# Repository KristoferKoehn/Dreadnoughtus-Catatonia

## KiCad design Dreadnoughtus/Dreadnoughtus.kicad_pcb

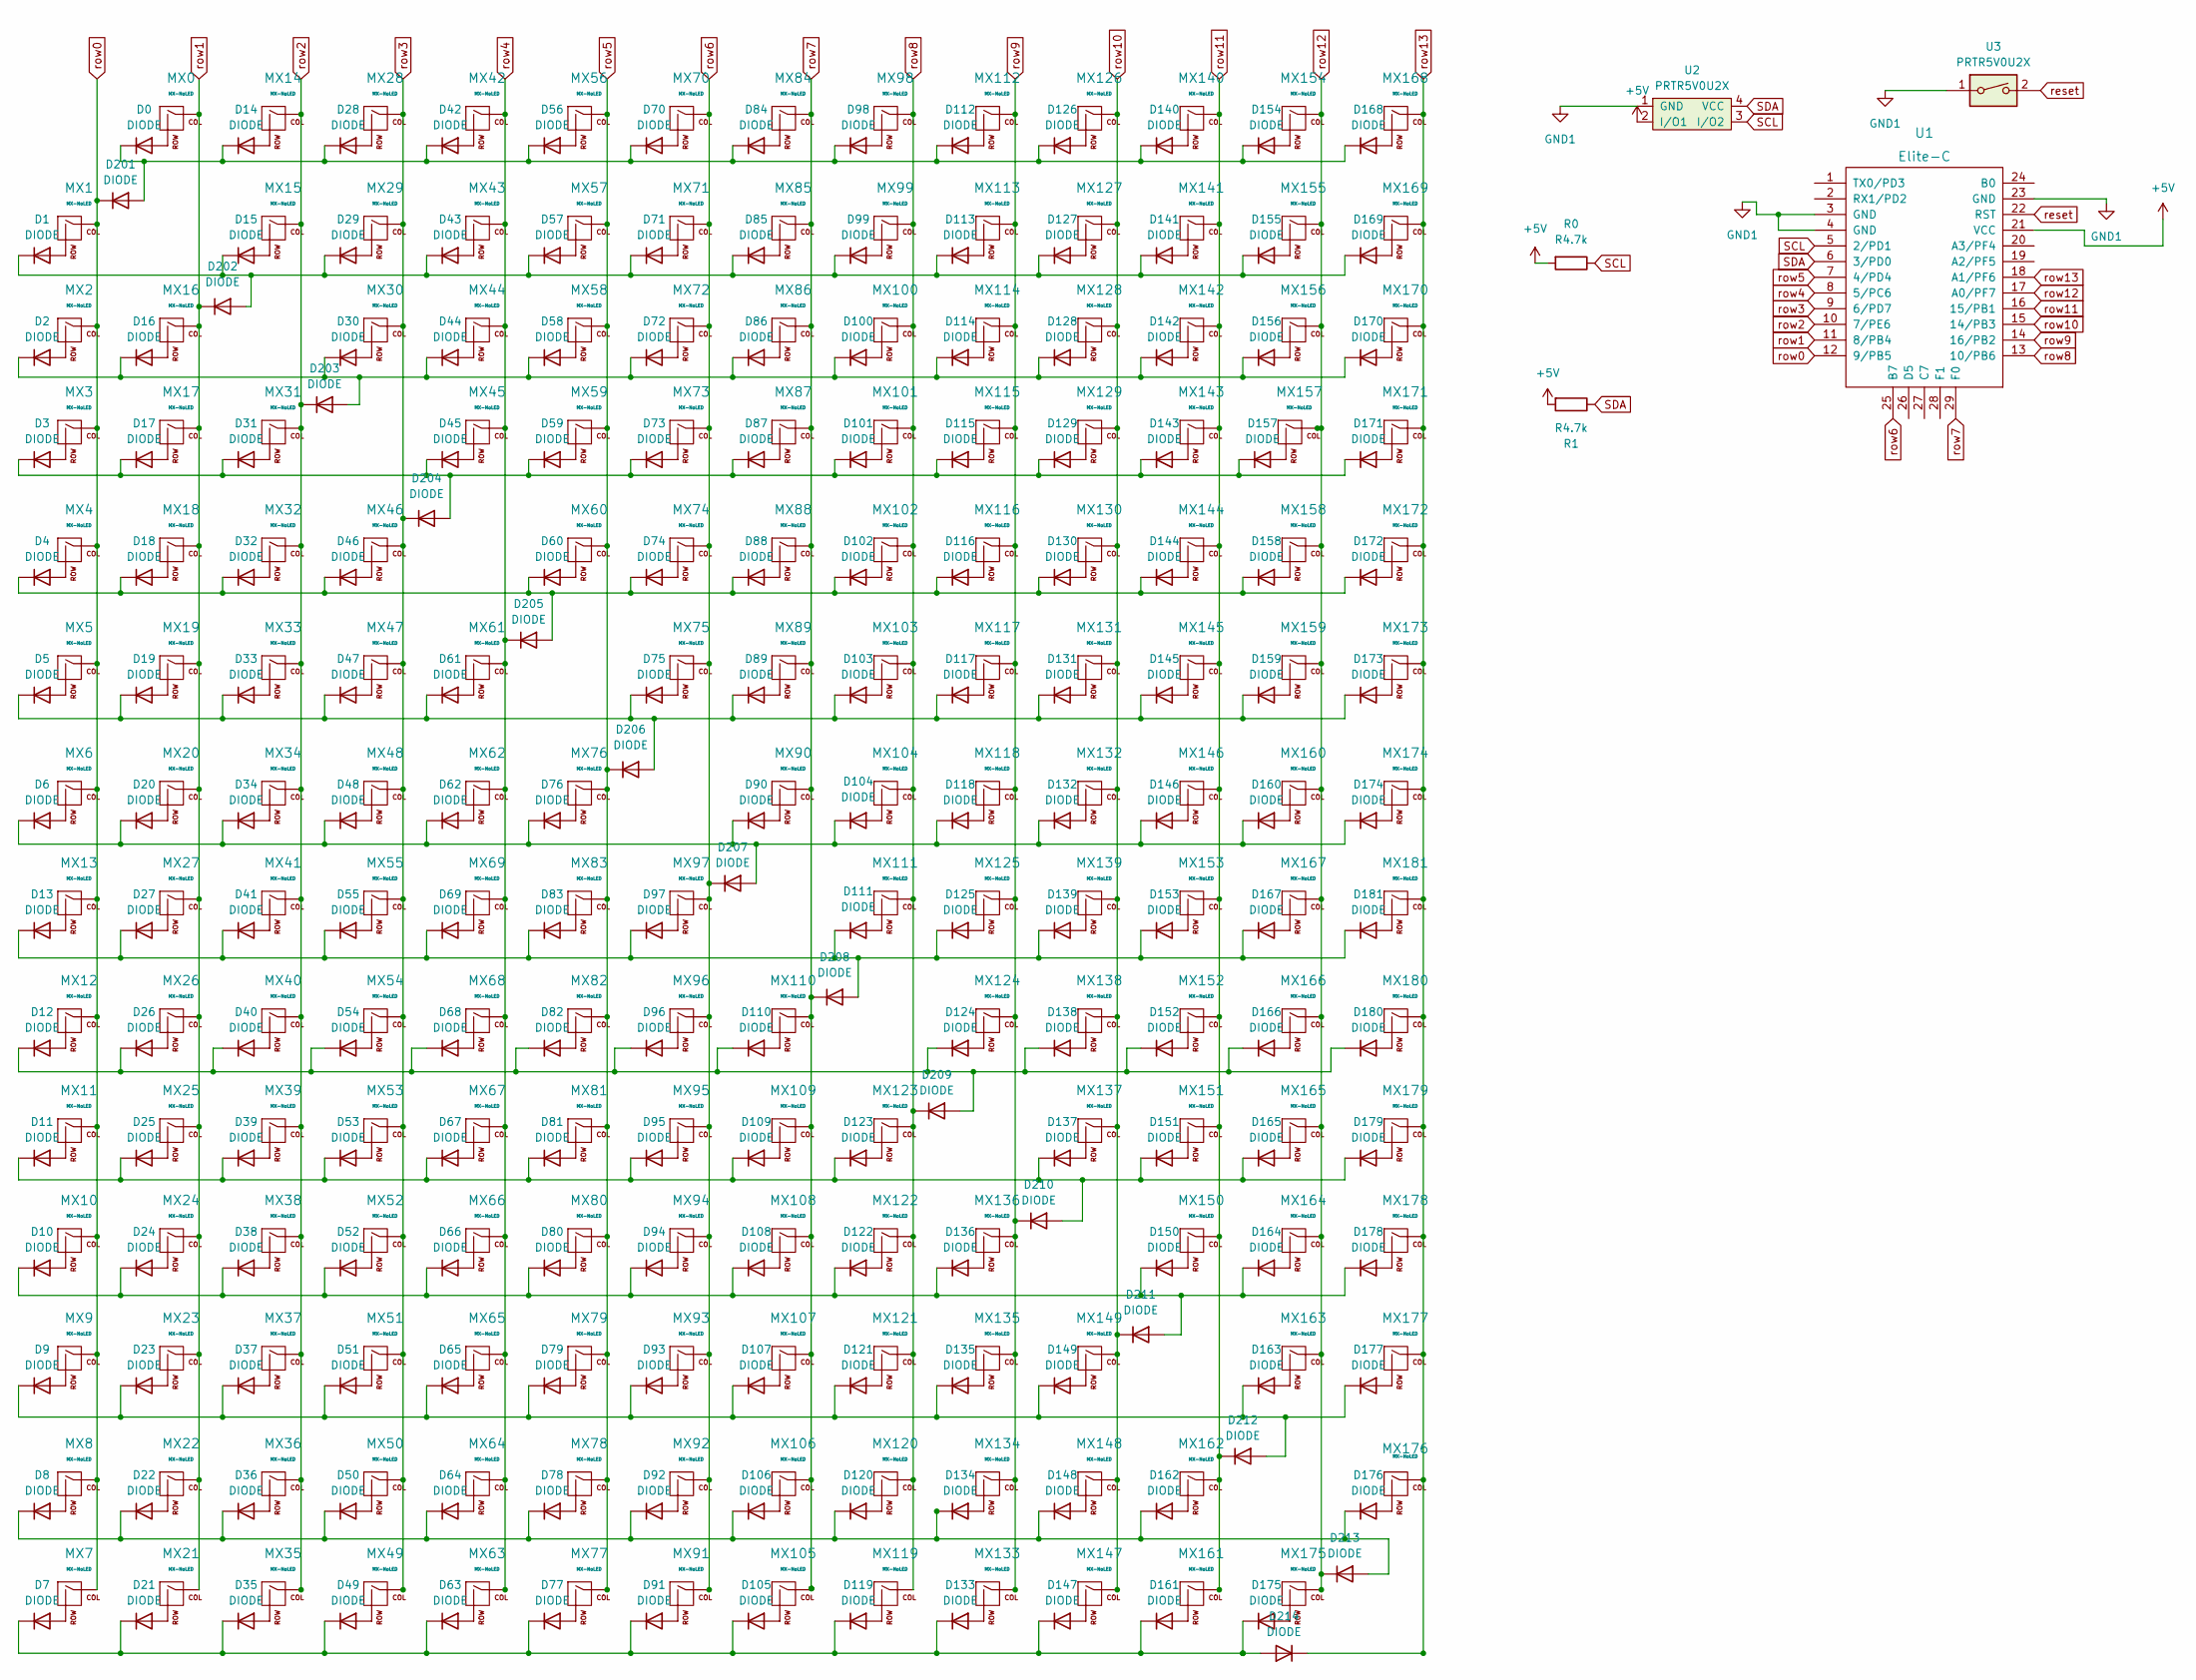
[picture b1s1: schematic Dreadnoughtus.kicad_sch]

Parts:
D0, D1, D2, D3, D4, D5, D6, D7, D8, D9, D10, D11, D12, D13, D14, D15, D16, D17, D18, D19, D20, D21, D22, D23, D24, D25, D26, D27, D28, D29, D30, D31, D32, D33, D34, D35, D36, D37, D38, D39, D40, D41, D42, D43, D44, D45, D46, D47, D48, D49, D50, D51, D52, D53, D54, D55, D56, D57, D58, D59, D60, D61, D62, D63, D64, D65, D66, D67, D68, D69, D70, D71, D72, D73, D74, D75, D76, D77, D78, D79, D80, D81, D82, D83, D84, D85, D86, D87, D88, D89, D90, D91, D92, D93, D94, D95, D96, D97, D98, D99, D100, D101, D102, D103, D104, D105, D106, D107, D108, D109, D110, D111, D112, D113, D114, D115, D116, D117, D118, D119, D120, D121, D122, D123, D124, D125, D126, D127, D128, D129, D130, D131, D132, D133, D134, D135, D136, D137, D138, D139, D140, D141, D142, D143, D144, D145, D146, D147, D148, D149, D150, D151, D152, D153, D154, D155, D156, D157, D158, D159, D160, D161, D162, D163, D164, D165, D166, D167, D168, D169, D170, D171, D172, D173, D174, D175, D176, D177, D178, D179, D180, D181, D201, D202, D203, D204, D205, D206, D207, D208, D209, D210, D211, D212, D213, D214: DIODE; Diode-dual
MX0, MX1, MX2, MX3, MX4, MX5, MX6, MX7, MX8, MX9, MX10, MX11, MX12, MX13, MX14, MX15, MX16, MX17, MX18, MX19, MX20, MX21, MX22, MX23, MX24, MX25, MX26, MX27, MX28, MX29, MX30, MX31, MX32, MX33, MX34, MX35, MX36, MX37, MX38, MX39, MX40, MX41, MX42, MX43, MX44, MX45, MX46, MX47, MX48, MX49, MX50, MX51, MX52, MX53, MX54, MX55, MX56, MX57, MX58, MX59, MX60, MX61, MX62, MX63, MX64, MX65, MX66, MX67, MX68, MX69, MX70, MX71, MX72, MX73, MX74, MX75, MX76, MX77, MX78, MX79, MX80, MX81, MX82, MX83, MX84, MX85, MX86, MX87, MX88, MX89, MX90, MX91, MX92, MX93, MX94, MX95, MX96, MX97, MX98, MX99, MX100, MX101, MX102, MX103, MX104, MX105, MX106, MX107, MX108, MX109, MX110, MX111, MX112, MX113, MX114, MX115, MX116, MX117, MX118, MX119, MX120, MX121, MX122, MX123, MX124, MX125, MX126, MX127, MX128, MX129, MX130, MX131, MX132, MX133, MX134, MX135, MX136, MX137, MX138, MX139, MX140, MX141, MX142, MX143, MX144, MX145, MX146, MX147, MX148, MX149, MX150, MX151, MX152, MX153, MX154, MX155, MX156, MX157, MX158, MX159, MX160, MX161, MX162, MX163, MX164, MX165, MX166, MX167, MX168, MX169, MX170, MX171, MX172, MX173, MX174, MX175, MX176, MX177, MX178, MX179, MX180, MX181: MX-NoLED; MXOnly-1U-Hotswap
R0, R1: R4.7k; Resistor
U1: Elite-C
U2: PRTR5V0U2X; I2C_Breakout
U3: PRTR5V0U2X; SW_Tactile_SPST_Angled_MJTP1117

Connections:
+5V: R0.2, R1.2, U1.21 (VCC), U2.2 (I/O1)
GND1: U1.3 (GND), U1.4 (GND), U1.23 (GND), U2.1 (GND), U3.1
unnamed: D0.1 (A), MX0.2 (ROW)
unnamed: D0.2 (K), D14.2 (K), D28.2 (K), D42.2 (K), D56.2 (K), D70.2 (K), D84.2 (K), D98.2 (K), D112.2 (K), D126.2 (K), D140.2 (K), D154.2 (K), D168.2 (K), D201.1 (A)
unnamed: D1.1 (A), MX1.2 (ROW)
unnamed: D1.2 (K), D15.2 (K), D29.2 (K), D43.2 (K), D57.2 (K), D71.2 (K), D85.2 (K), D99.2 (K), D113.2 (K), D127.2 (K), D141.2 (K), D155.2 (K), D169.2 (K), D202.1 (A)
unnamed: D2.1 (A), MX2.2 (ROW)
unnamed: D3.1 (A), MX3.2 (ROW)
unnamed: D4.1 (A), MX4.2 (ROW)
unnamed: D5.1 (A), MX5.2 (ROW)
unnamed: D6.1 (A), MX6.2 (ROW)
unnamed: D7.1 (A), MX7.2 (ROW)
unnamed: D8.1 (A), MX8.2 (ROW)
unnamed: D9.1 (A), MX9.2 (ROW)
unnamed: D10.1 (A), MX10.2 (ROW)
unnamed: D10.2 (K), D24.2 (K), D38.2 (K), D52.2 (K), D66.2 (K), D80.2 (K), D94.2 (K), D108.2 (K), D122.2 (K), D136.2 (K), D150.2 (K), D164.2 (K), D178.2 (K), D211.1 (A)
unnamed: D11.1 (A), MX11.2 (ROW)
unnamed: D12.1 (A), MX12.2 (ROW)
unnamed: D13.1 (A), MX13.2 (ROW)
unnamed: D14.1 (A), MX14.2 (ROW)
unnamed: D15.1 (A), MX15.2 (ROW)
unnamed: D16.1 (A), MX16.2 (ROW)
unnamed: D17.1 (A), MX17.2 (ROW)
unnamed: D18.1 (A), MX18.2 (ROW)
unnamed: D19.1 (A), MX19.2 (ROW)
unnamed: D20.1 (A), MX20.2 (ROW)
unnamed: D21.1 (A), MX21.2 (ROW)
unnamed: D22.1 (A), MX22.2 (ROW)
unnamed: D23.1 (A), MX23.2 (ROW)
unnamed: D24.1 (A), MX24.2 (ROW)
unnamed: D25.1 (A), MX25.2 (ROW)
unnamed: D26.1 (A), MX26.2 (ROW)
unnamed: D27.1 (A), MX27.2 (ROW)
unnamed: D28.1 (A), MX28.2 (ROW)
unnamed: D29.1 (A), MX29.2 (ROW)
unnamed: D30.1 (A), MX30.2 (ROW)
unnamed: D31.1 (A), MX31.2 (ROW)
unnamed: D32.1 (A), MX32.2 (ROW)
unnamed: D33.1 (A), MX33.2 (ROW)
unnamed: D34.1 (A), MX34.2 (ROW)
unnamed: D35.1 (A), MX35.2 (ROW)
unnamed: D36.1 (A), MX36.2 (ROW)
unnamed: D37.1 (A), MX37.2 (ROW)
unnamed: D38.1 (A), MX38.2 (ROW)
unnamed: D39.1 (A), MX39.2 (ROW)
unnamed: D40.1 (A), MX40.2 (ROW)
unnamed: D41.1 (A), MX41.2 (ROW)
unnamed: D42.1 (A), MX42.2 (ROW)
unnamed: D43.1 (A), MX43.2 (ROW)
unnamed: D44.1 (A), MX44.2 (ROW)
unnamed: D45.1 (A), MX45.2 (ROW)
unnamed: D46.1 (A), MX46.2 (ROW)
unnamed: D47.1 (A), MX47.2 (ROW)
unnamed: D48.1 (A), MX48.2 (ROW)
unnamed: D49.1 (A), MX49.2 (ROW)
unnamed: D50.1 (A), MX50.2 (ROW)
unnamed: D51.1 (A), MX51.2 (ROW)
unnamed: D52.1 (A), MX52.2 (ROW)
unnamed: D53.1 (A), MX53.2 (ROW)
unnamed: D54.1 (A), MX54.2 (ROW)
unnamed: D55.1 (A), MX55.2 (ROW)
unnamed: D56.1 (A), MX56.2 (ROW)
unnamed: D57.1 (A), MX57.2 (ROW)
unnamed: D58.1 (A), MX58.2 (ROW)
unnamed: D59.1 (A), MX59.2 (ROW)
unnamed: D60.1 (A), MX60.2 (ROW)
unnamed: D61.1 (A), MX61.2 (ROW)
unnamed: D62.1 (A), MX62.2 (ROW)
unnamed: D63.1 (A), MX63.2 (ROW)
unnamed: D64.1 (A), MX64.2 (ROW)
unnamed: D65.1 (A), MX65.2 (ROW)
unnamed: D66.1 (A), MX66.2 (ROW)
unnamed: D67.1 (A), MX67.2 (ROW)
unnamed: D68.1 (A), MX68.2 (ROW)
unnamed: D69.1 (A), MX69.2 (ROW)
unnamed: D70.1 (A), MX70.2 (ROW)
unnamed: D71.1 (A), MX71.2 (ROW)
unnamed: D72.1 (A), MX72.2 (ROW)
unnamed: D73.1 (A), MX73.2 (ROW)
unnamed: D74.1 (A), MX74.2 (ROW)
unnamed: D75.1 (A), MX75.2 (ROW)
unnamed: D76.1 (A), MX76.2 (ROW)
unnamed: D77.1 (A), MX77.2 (ROW)
unnamed: D78.1 (A), MX78.2 (ROW)
unnamed: D79.1 (A), MX79.2 (ROW)
unnamed: D80.1 (A), MX80.2 (ROW)
unnamed: D81.1 (A), MX81.2 (ROW)
unnamed: D82.1 (A), MX82.2 (ROW)
unnamed: D83.1 (A), MX83.2 (ROW)
unnamed: D84.1 (A), MX84.2 (ROW)
unnamed: D85.1 (A), MX85.2 (ROW)
unnamed: D86.1 (A), MX86.2 (ROW)
unnamed: D87.1 (A), MX87.2 (ROW)
unnamed: D88.1 (A), MX88.2 (ROW)
unnamed: D89.1 (A), MX89.2 (ROW)
unnamed: D90.1 (A), MX90.2 (ROW)
unnamed: D91.1 (A), MX91.2 (ROW)
unnamed: D92.1 (A), MX92.2 (ROW)
unnamed: D93.1 (A), MX93.2 (ROW)
unnamed: D94.1 (A), MX94.2 (ROW)
unnamed: D95.1 (A), MX95.2 (ROW)
unnamed: D96.1 (A), MX96.2 (ROW)
unnamed: D97.1 (A), MX97.2 (ROW)
unnamed: D98.1 (A), MX98.2 (ROW)
unnamed: D99.1 (A), MX99.2 (ROW)
unnamed: D100.1 (A), MX100.2 (ROW)
unnamed: D2.2 (K), D16.2 (K), D30.2 (K), D44.2 (K), D58.2 (K), D72.2 (K), D86.2 (K), D100.2 (K), D114.2 (K), D128.2 (K), D142.2 (K), D156.2 (K), D170.2 (K), D203.1 (A)
unnamed: D101.1 (A), MX101.2 (ROW)
unnamed: D3.2 (K), D17.2 (K), D31.2 (K), D45.2 (K), D59.2 (K), D73.2 (K), D87.2 (K), D101.2 (K), D115.2 (K), D129.2 (K), D143.2 (K), D157.2 (K), D171.2 (K), D204.1 (A)
unnamed: D102.1 (A), MX102.2 (ROW)
unnamed: D4.2 (K), D18.2 (K), D32.2 (K), D46.2 (K), D60.2 (K), D74.2 (K), D88.2 (K), D102.2 (K), D116.2 (K), D130.2 (K), D144.2 (K), D158.2 (K), D172.2 (K), D205.1 (A)
unnamed: D103.1 (A), MX103.2 (ROW)
unnamed: D5.2 (K), D19.2 (K), D33.2 (K), D47.2 (K), D61.2 (K), D75.2 (K), D89.2 (K), D103.2 (K), D117.2 (K), D131.2 (K), D145.2 (K), D159.2 (K), D173.2 (K), D206.1 (A)
unnamed: D104.1 (A), MX104.2 (ROW)
unnamed: D6.2 (K), D20.2 (K), D34.2 (K), D48.2 (K), D62.2 (K), D76.2 (K), D90.2 (K), D104.2 (K), D118.2 (K), D132.2 (K), D146.2 (K), D160.2 (K), D174.2 (K), D207.1 (A)
unnamed: D105.1 (A), MX105.2 (ROW)
unnamed: D7.2 (K), D21.2 (K), D35.2 (K), D49.2 (K), D63.2 (K), D77.2 (K), D91.2 (K), D105.2 (K), D119.2 (K), D133.2 (K), D147.2 (K), D161.2 (K), D175.2 (K), D214.1 (A)
unnamed: D106.1 (A), MX106.2 (ROW)
unnamed: D8.2 (K), D22.2 (K), D36.2 (K), D50.2 (K), D64.2 (K), D78.2 (K), D92.2 (K), D106.2 (K), D120.2 (K), D134.2 (K), D148.2 (K), D162.2 (K), D176.2 (K), D213.1 (A)
unnamed: D107.1 (A), MX107.2 (ROW)
unnamed: D9.2 (K), D23.2 (K), D37.2 (K), D51.2 (K), D65.2 (K), D79.2 (K), D93.2 (K), D107.2 (K), D121.2 (K), D135.2 (K), D149.2 (K), D163.2 (K), D177.2 (K), D212.1 (A)
unnamed: D108.1 (A), MX108.2 (ROW)
unnamed: D109.1 (A), MX109.2 (ROW)
unnamed: D11.2 (K), D25.2 (K), D39.2 (K), D53.2 (K), D67.2 (K), D81.2 (K), D95.2 (K), D109.2 (K), D123.2 (K), D137.2 (K), D151.2 (K), D165.2 (K), D179.2 (K), D210.1 (A)
unnamed: D110.1 (A), MX110.2 (ROW)
unnamed: D12.2 (K), D26.2 (K), D40.2 (K), D54.2 (K), D68.2 (K), D82.2 (K), D96.2 (K), D110.2 (K), D124.2 (K), D138.2 (K), D152.2 (K), D166.2 (K), D180.2 (K), D209.1 (A)
unnamed: D111.1 (A), MX111.2 (ROW)
unnamed: D13.2 (K), D27.2 (K), D41.2 (K), D55.2 (K), D69.2 (K), D83.2 (K), D97.2 (K), D111.2 (K), D125.2 (K), D139.2 (K), D153.2 (K), D167.2 (K), D181.2 (K), D208.1 (A)
unnamed: D112.1 (A), MX112.2 (ROW)
unnamed: D113.1 (A), MX113.2 (ROW)
unnamed: D114.1 (A), MX114.2 (ROW)
unnamed: D115.1 (A), MX115.2 (ROW)
unnamed: D116.1 (A), MX116.2 (ROW)
unnamed: D117.1 (A), MX117.2 (ROW)
unnamed: D118.1 (A), MX118.2 (ROW)
unnamed: D119.1 (A), MX119.2 (ROW)
unnamed: D120.1 (A), MX120.2 (ROW)
unnamed: D121.1 (A), MX121.2 (ROW)
unnamed: D122.1 (A), MX122.2 (ROW)
unnamed: D123.1 (A), MX123.2 (ROW)
unnamed: D124.1 (A), MX124.2 (ROW)
unnamed: D125.1 (A), MX125.2 (ROW)
unnamed: D126.1 (A), MX126.2 (ROW)
unnamed: D127.1 (A), MX127.2 (ROW)
unnamed: D128.1 (A), MX128.2 (ROW)
unnamed: D129.1 (A), MX129.2 (ROW)
unnamed: D130.1 (A), MX130.2 (ROW)
unnamed: D131.1 (A), MX131.2 (ROW)
unnamed: D132.1 (A), MX132.2 (ROW)
unnamed: D133.1 (A), MX133.2 (ROW)
unnamed: D134.1 (A), MX134.2 (ROW)
unnamed: D135.1 (A), MX135.2 (ROW)
unnamed: D136.1 (A), MX136.2 (ROW)
unnamed: D137.1 (A), MX137.2 (ROW)
unnamed: D138.1 (A), MX138.2 (ROW)
unnamed: D139.1 (A), MX139.2 (ROW)
unnamed: D140.1 (A), MX140.2 (ROW)
unnamed: D141.1 (A), MX141.2 (ROW)
unnamed: D142.1 (A), MX142.2 (ROW)
unnamed: D143.1 (A), MX143.2 (ROW)
unnamed: D144.1 (A), MX144.2 (ROW)
unnamed: D145.1 (A), MX145.2 (ROW)
unnamed: D146.1 (A), MX146.2 (ROW)
unnamed: D147.1 (A), MX147.2 (ROW)
unnamed: D148.1 (A), MX148.2 (ROW)
unnamed: D149.1 (A), MX149.2 (ROW)
unnamed: D150.1 (A), MX150.2 (ROW)
unnamed: D151.1 (A), MX151.2 (ROW)
unnamed: D152.1 (A), MX152.2 (ROW)
unnamed: D153.1 (A), MX153.2 (ROW)
unnamed: D154.1 (A), MX154.2 (ROW)
unnamed: D155.1 (A), MX155.2 (ROW)
unnamed: D156.1 (A), MX156.2 (ROW)
unnamed: D157.1 (A), MX157.2 (ROW)
unnamed: D158.1 (A), MX158.2 (ROW)
unnamed: D159.1 (A), MX159.2 (ROW)
unnamed: D160.1 (A), MX160.2 (ROW)
unnamed: D161.1 (A), MX161.2 (ROW)
unnamed: D162.1 (A), MX162.2 (ROW)
unnamed: D163.1 (A), MX163.2 (ROW)
unnamed: D164.1 (A), MX164.2 (ROW)
unnamed: D165.1 (A), MX165.2 (ROW)
unnamed: D166.1 (A), MX166.2 (ROW)
unnamed: D167.1 (A), MX167.2 (ROW)
unnamed: D168.1 (A), MX168.2 (ROW)
unnamed: D169.1 (A), MX169.2 (ROW)
unnamed: D170.1 (A), MX170.2 (ROW)
unnamed: D171.1 (A), MX171.2 (ROW)
unnamed: D172.1 (A), MX172.2 (ROW)
unnamed: D173.1 (A), MX173.2 (ROW)
unnamed: D174.1 (A), MX174.2 (ROW)
unnamed: D175.1 (A), MX175.2 (ROW)
unnamed: D176.1 (A), MX176.2 (ROW)
unnamed: D177.1 (A), MX177.2 (ROW)
unnamed: D178.1 (A), MX178.2 (ROW)
unnamed: D179.1 (A), MX179.2 (ROW)
unnamed: D180.1 (A), MX180.2 (ROW)
unnamed: D181.1 (A), MX181.2 (ROW)
SCL: R0.1, U1.5 (2/PD1), U2.3 (I/O2)
SDA: R1.1, U1.6 (3/PD0), U2.4 (VCC)
reset: U1.22 (RST), U3.2
row0: D201.2 (K), MX1.1 (COL), MX2.1 (COL), MX3.1 (COL), MX4.1 (COL), MX5.1 (COL), MX6.1 (COL), MX7.1 (COL), MX8.1 (COL), MX9.1 (COL), MX10.1 (COL), MX11.1 (COL), MX12.1 (COL), MX13.1 (COL), U1.12 (9/PB5)
row1: D202.2 (K), MX0.1 (COL), MX16.1 (COL), MX17.1 (COL), MX18.1 (COL), MX19.1 (COL), MX20.1 (COL), MX21.1 (COL), MX22.1 (COL), MX23.1 (COL), MX24.1 (COL), MX25.1 (COL), MX26.1 (COL), MX27.1 (COL), U1.11 (8/PB4)
row2: D203.2 (K), MX14.1 (COL), MX15.1 (COL), MX31.1 (COL), MX32.1 (COL), MX33.1 (COL), MX34.1 (COL), MX35.1 (COL), MX36.1 (COL), MX37.1 (COL), MX38.1 (COL), MX39.1 (COL), MX40.1 (COL), MX41.1 (COL), U1.10 (7/PE6)
row3: D204.2 (K), MX28.1 (COL), MX29.1 (COL), MX30.1 (COL), MX46.1 (COL), MX47.1 (COL), MX48.1 (COL), MX49.1 (COL), MX50.1 (COL), MX51.1 (COL), MX52.1 (COL), MX53.1 (COL), MX54.1 (COL), MX55.1 (COL), U1.9 (6/PD7)
row4: D205.2 (K), MX42.1 (COL), MX43.1 (COL), MX44.1 (COL), MX45.1 (COL), MX61.1 (COL), MX62.1 (COL), MX63.1 (COL), MX64.1 (COL), MX65.1 (COL), MX66.1 (COL), MX67.1 (COL), MX68.1 (COL), MX69.1 (COL), U1.8 (5/PC6)
row5: D206.2 (K), MX56.1 (COL), MX57.1 (COL), MX58.1 (COL), MX59.1 (COL), MX60.1 (COL), MX76.1 (COL), MX77.1 (COL), MX78.1 (COL), MX79.1 (COL), MX80.1 (COL), MX81.1 (COL), MX82.1 (COL), MX83.1 (COL), U1.7 (4/PD4)
row6: D207.2 (K), MX70.1 (COL), MX71.1 (COL), MX72.1 (COL), MX73.1 (COL), MX74.1 (COL), MX75.1 (COL), MX91.1 (COL), MX92.1 (COL), MX93.1 (COL), MX94.1 (COL), MX95.1 (COL), MX96.1 (COL), MX97.1 (COL), U1.25 (B7)
row7: D208.2 (K), MX84.1 (COL), MX85.1 (COL), MX86.1 (COL), MX87.1 (COL), MX88.1 (COL), MX89.1 (COL), MX90.1 (COL), MX105.1 (COL), MX106.1 (COL), MX107.1 (COL), MX108.1 (COL), MX109.1 (COL), MX110.1 (COL), U1.29 (F0)
row8: D209.2 (K), MX98.1 (COL), MX99.1 (COL), MX100.1 (COL), MX101.1 (COL), MX102.1 (COL), MX103.1 (COL), MX104.1 (COL), MX111.1 (COL), MX119.1 (COL), MX120.1 (COL), MX121.1 (COL), MX122.1 (COL), MX123.1 (COL), U1.13 (10/PB6)
row9: D210.2 (K), MX112.1 (COL), MX113.1 (COL), MX114.1 (COL), MX115.1 (COL), MX116.1 (COL), MX117.1 (COL), MX118.1 (COL), MX124.1 (COL), MX125.1 (COL), MX133.1 (COL), MX134.1 (COL), MX135.1 (COL), MX136.1 (COL), U1.14 (16/PB2)
row10: D211.2 (K), MX126.1 (COL), MX127.1 (COL), MX128.1 (COL), MX129.1 (COL), MX130.1 (COL), MX131.1 (COL), MX132.1 (COL), MX137.1 (COL), MX138.1 (COL), MX139.1 (COL), MX147.1 (COL), MX148.1 (COL), MX149.1 (COL), U1.15 (14/PB3)
row11: D212.2 (K), MX140.1 (COL), MX141.1 (COL), MX142.1 (COL), MX143.1 (COL), MX144.1 (COL), MX145.1 (COL), MX146.1 (COL), MX150.1 (COL), MX151.1 (COL), MX152.1 (COL), MX153.1 (COL), MX161.1 (COL), MX162.1 (COL), U1.16 (15/PB1)
row12: D213.2 (K), MX154.1 (COL), MX155.1 (COL), MX156.1 (COL), MX157.1 (COL), MX158.1 (COL), MX159.1 (COL), MX160.1 (COL), MX163.1 (COL), MX164.1 (COL), MX165.1 (COL), MX166.1 (COL), MX167.1 (COL), MX175.1 (COL), U1.17 (A0/PF7)
row13: D214.2 (K), MX168.1 (COL), MX169.1 (COL), MX170.1 (COL), MX171.1 (COL), MX172.1 (COL), MX173.1 (COL), MX174.1 (COL), MX176.1 (COL), MX177.1 (COL), MX178.1 (COL), MX179.1 (COL), MX180.1 (COL), MX181.1 (COL), U1.18 (A1/PF6)

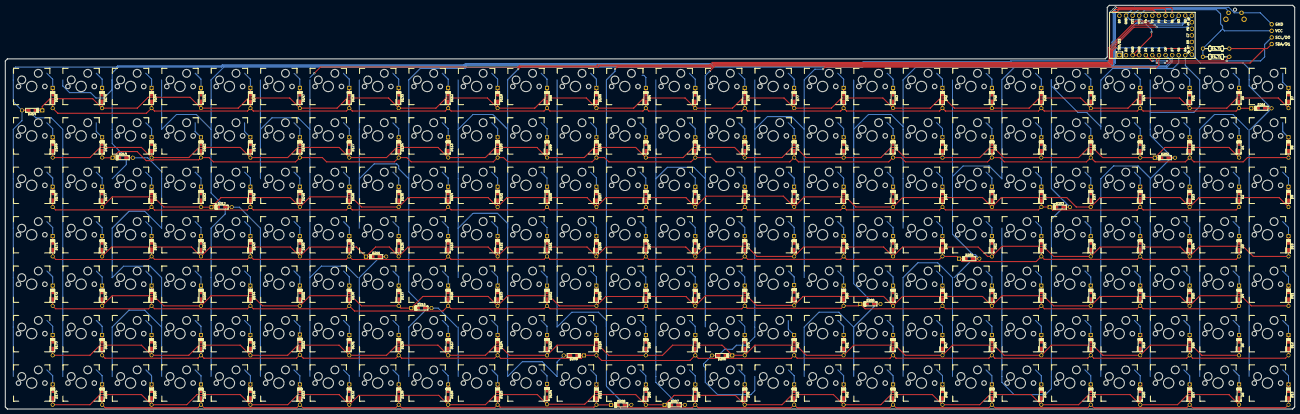
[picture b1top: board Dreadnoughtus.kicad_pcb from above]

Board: 2 copper layers, 496.9 x 155.6 mm, 383 parts (1 on the bottom side), 215 nets.

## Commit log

2022-08-02 added keebio symbols
2022-08-03 finalizing matrix
2022-08-04 added keebio components
2022-08-05 finalized matrix connections
2022-08-05 named switches and switch diodes, added i2c start schematic
2022-08-06 arranged switches on pcb
2022-08-06 tracked most switches and diodes
2022-08-06 rev 0 push, first completion
2022-08-07 small tweak to I2C breakout position
2022-08-08 another final touch
2022-08-10 small touch
2022-08-10 added untested firmware
2022-08-11 updated firmware
